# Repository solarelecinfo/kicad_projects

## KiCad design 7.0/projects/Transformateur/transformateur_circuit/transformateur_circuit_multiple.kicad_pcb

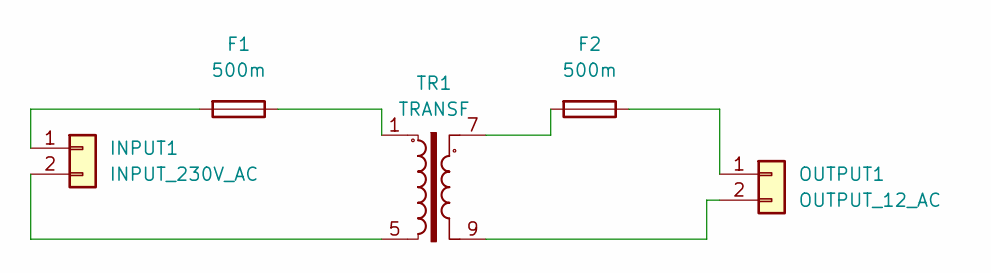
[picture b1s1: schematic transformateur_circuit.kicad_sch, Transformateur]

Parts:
F1, F2: 500m; CP_Axial_L21.0mm_D8.0mm_P28.00mm_Horizontal
INPUT1: INPUT_230V_AC; TerminalBlock_MetzConnect_Type094_RT03502HBLU_1x02_P5.00mm_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
OUTPUT1: OUTPUT_12_AC; TerminalBlock_MetzConnect_Type094_RT03502HBLU_1x02_P5.00mm_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
TR1: TRANSF; Transformer_Breve_TEZ-38x45

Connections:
unnamed: F1.1, TR1.1
unnamed: F2.2, TR1.7
unnamed: F1.2, INPUT1.1
unnamed: INPUT1.2, TR1.5
unnamed: F2.1, OUTPUT1.1
unnamed: OUTPUT1.2, TR1.9

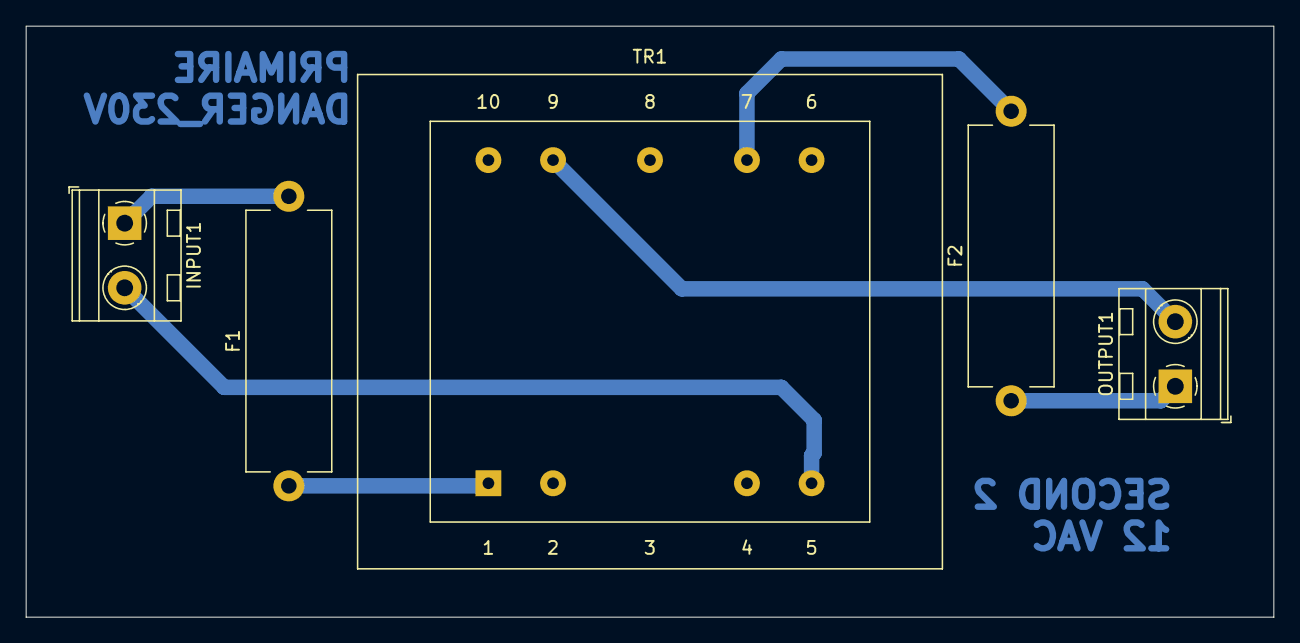
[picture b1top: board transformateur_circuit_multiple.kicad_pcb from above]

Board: 2 copper layers, 96.5 x 45.7 mm, 5 parts (0 on the bottom side), 6 nets.

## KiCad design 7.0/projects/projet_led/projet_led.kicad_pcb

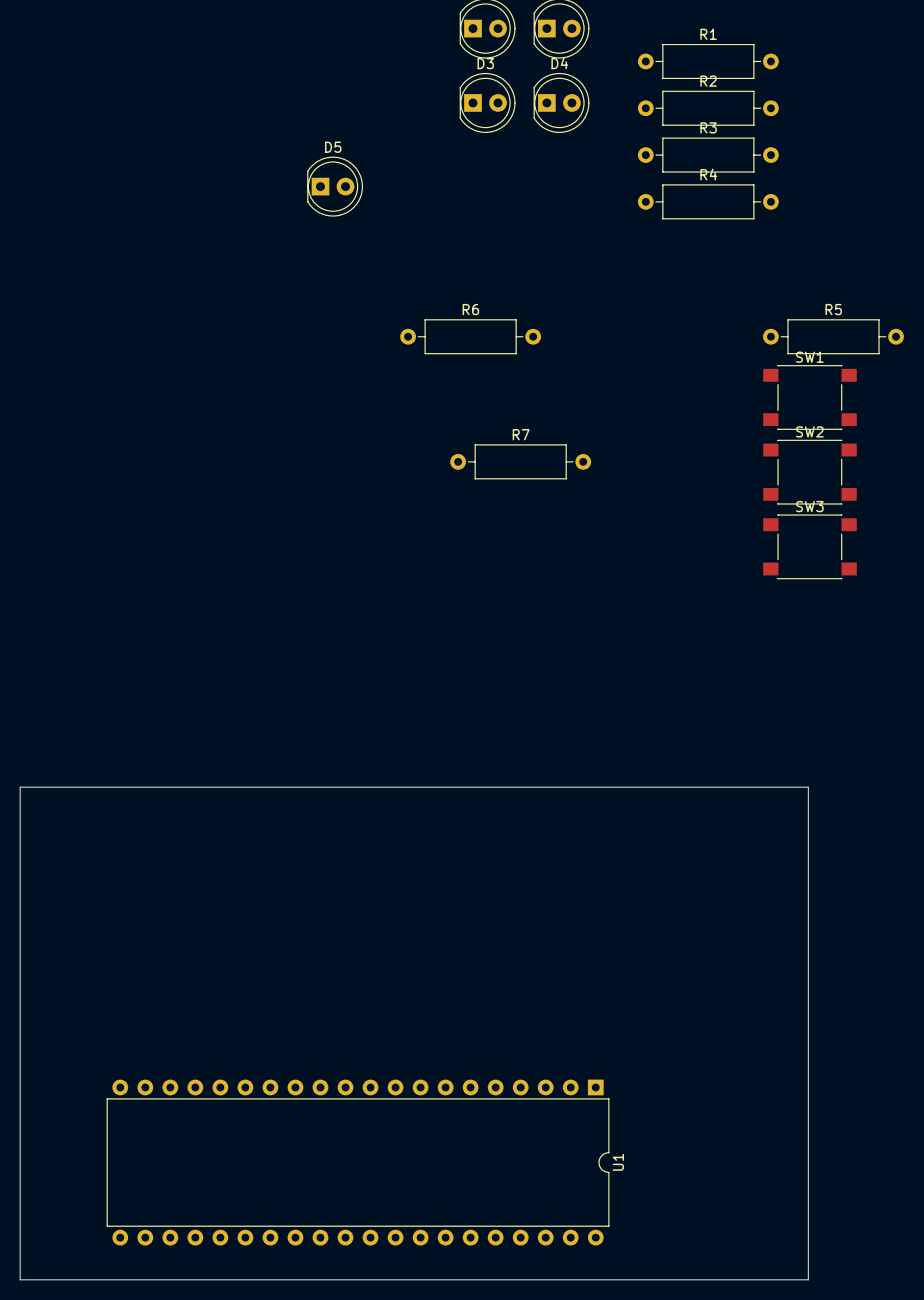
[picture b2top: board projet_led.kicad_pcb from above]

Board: 2 copper layers, 80.0 x 50.0 mm, 16 parts (0 on the bottom side), 15 nets, no tracks yet.

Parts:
D1, D2, D3, D4, D5: LD271; LED_D5.0mm_IRGrey
R1: 600 ohm; R_Axial_DIN0309_L9.0mm_D3.2mm_P12.70mm_Horizontal
R2, R3, R4: R; R_Axial_DIN0309_L9.0mm_D3.2mm_P12.70mm_Horizontal
R5, R6, R7: 30K; R_Axial_DIN0309_L9.0mm_D3.2mm_P12.70mm_Horizontal
SW1, SW2, SW3: SW_Push; SW_Push_1P1T_NO_6x6mm_H9.5mm
U1: ATmega32-16P; DIP-40_W15.24mm

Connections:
+1V5: R5.1, SW2.2, SW3.2, U1.10 (VCC)
/MANGO: R6.1, R7.1
/chepe: D5.2 (A), R6.2, R7.2
GND: D1.1 (K), D2.1 (K), D3.1 (K), D4.1 (K), SW1.1, U1.11 (GND), U1.31 (GND)
unnamed: D1.2 (A), R1.1
unnamed: D2.2 (A), R2.1
unnamed: D3.2 (A), R3.1
unnamed: D4.2 (A), R4.1
unnamed: R1.2, U1.1 (PB0)
unnamed: R2.2, U1.2 (PB1)
unnamed: R3.2, U1.3 (PB2)
unnamed: R4.2, U1.4 (PB3)
unnamed: SW2.1, U1.22 (PC0)
unnamed: SW3.1, U1.23 (PC1)
unnamed: R5.2, SW1.2, U1.9 (~RESET)
